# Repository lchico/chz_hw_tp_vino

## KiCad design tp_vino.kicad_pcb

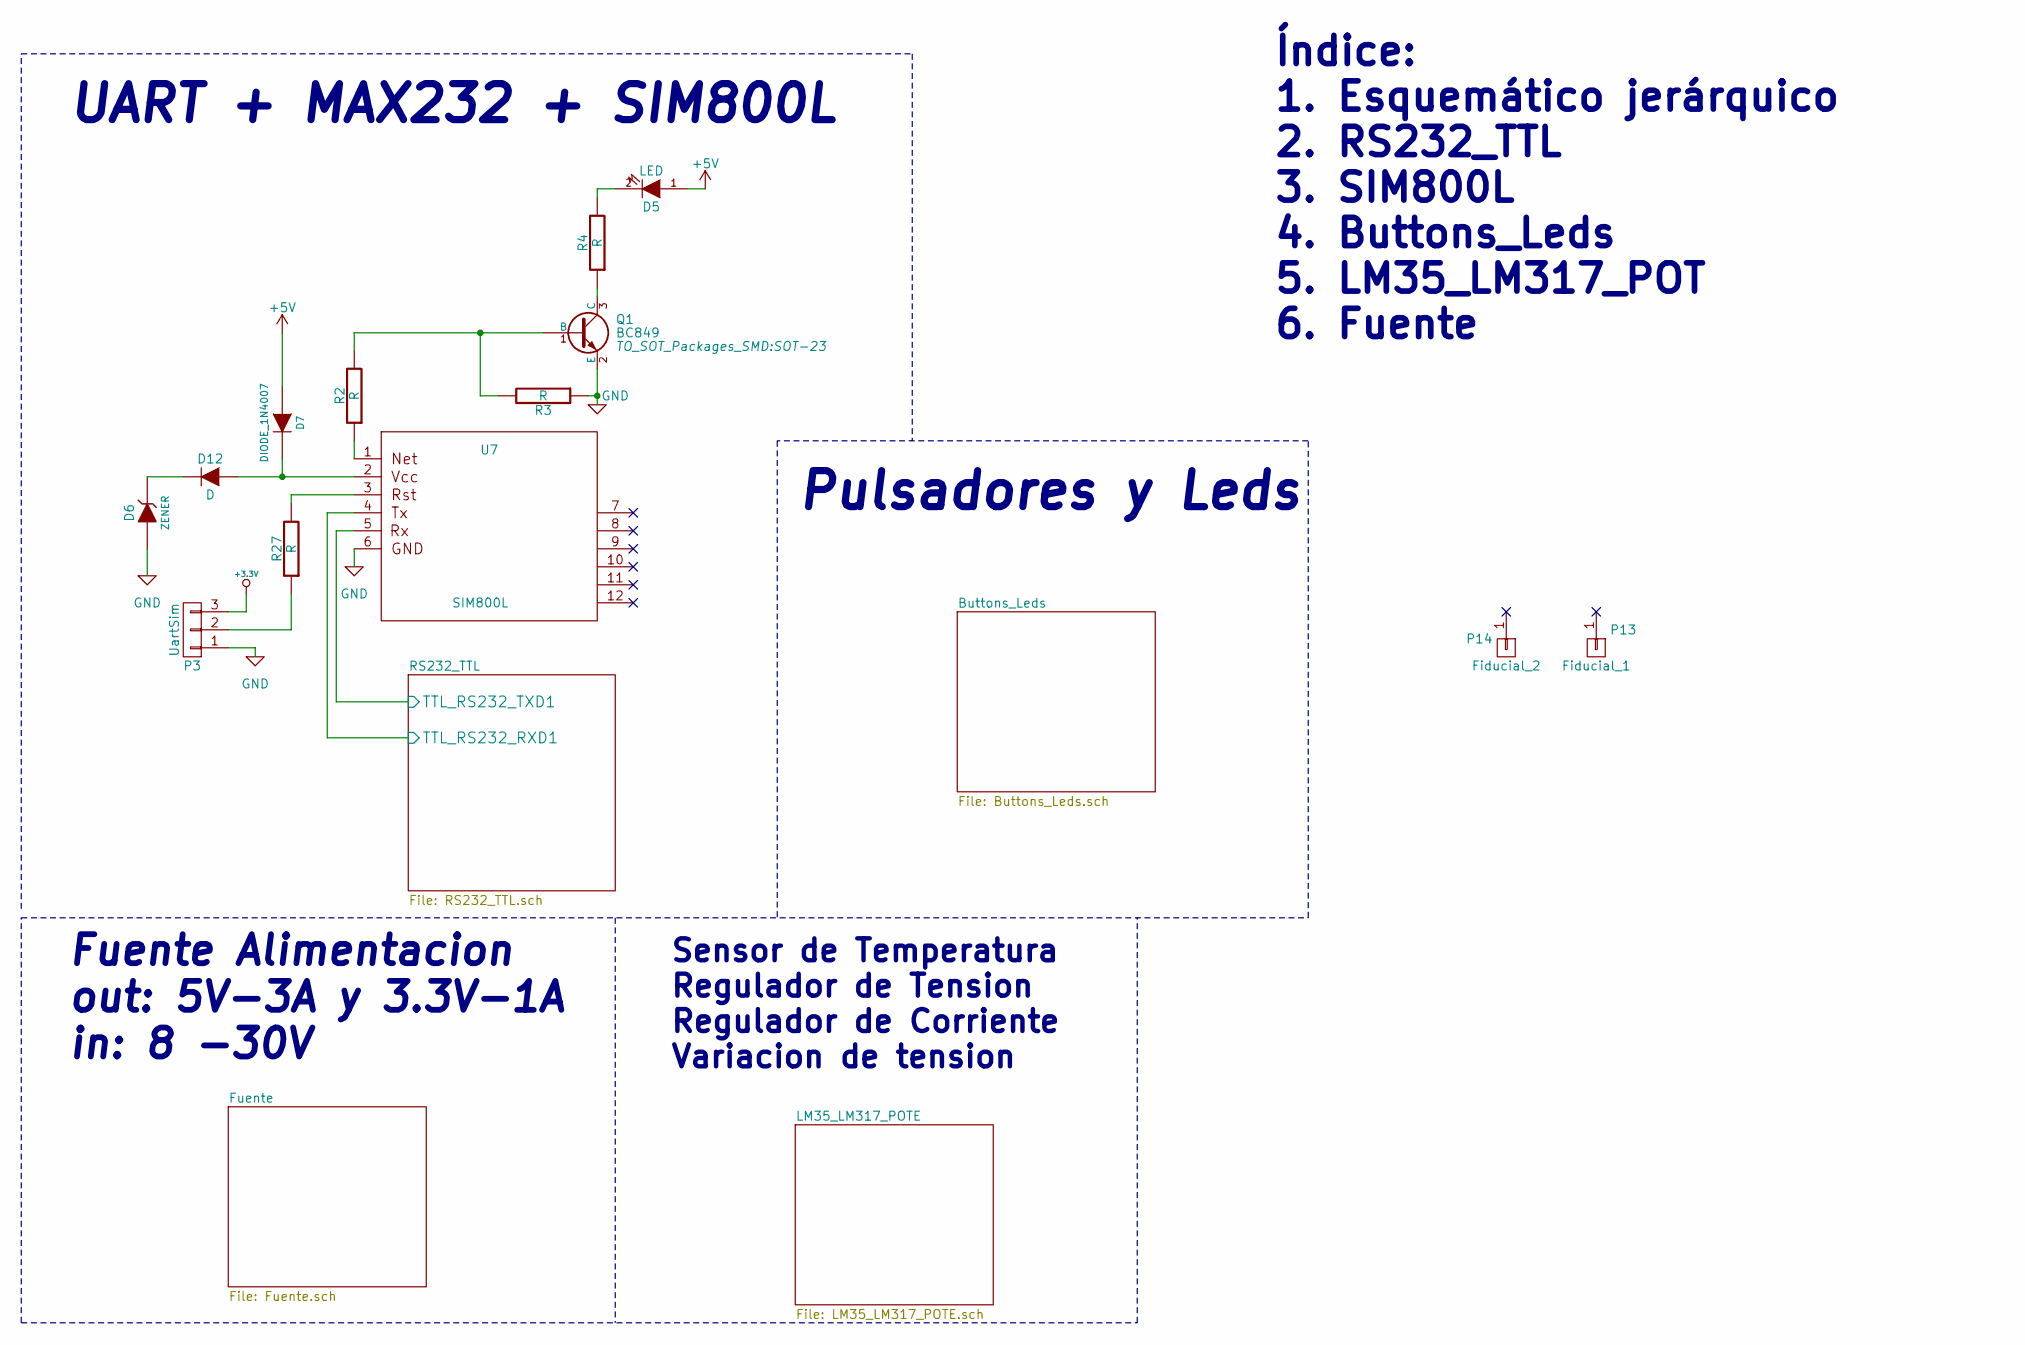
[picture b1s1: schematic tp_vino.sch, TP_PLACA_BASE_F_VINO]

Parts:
D5: LED; SMD-1206_Pol; Digikey SML-LX1206GC-TR SML-LX1206GC-TR
D6: ZENER; MELF_Standard
D7: DIODE_1N4007; MELF_Standard
D12: D; MELF_Standard
P3: UartSim; Pin_Header_Straight_1x03
P13: Fiducial_1
P14: Fiducial_2
Q1: BC849; SOT-23; Digikey# BC849BLT1GOSTR-ND
R2, R3, R4, R27: R; SMD-1206_Pol; Digikey# CRCW12060000Z0EA
U7: SIM800L; sim; Digikey# 1471-1458-ND

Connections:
+5V: D5.1 (A), D7.1 (A); also elsewhere on the board
/RS232_TTL/TTL_RS232_RXD1: U7.4; also elsewhere on the board
/RS232_TTL/TTL_RS232_TXD1: U7.5; also elsewhere on the board
GND: D6.1 (A), P3.1, Q1.2 (E), R3.1, U7.6; also elsewhere on the board
unnamed: D5.2 (K), R4.2
unnamed: D6.2 (K), D12.1 (K)
unnamed: D7.2 (K), D12.2 (A), U7.2
unnamed: P3.2, R27.1
unnamed: Q1.1 (B), R2.2, R3.2
unnamed: Q1.3 (C), R4.1
unnamed: R2.1, U7.1
unnamed: R27.2, U7.3

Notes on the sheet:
Índice: 1. Esquemático jerárquico 2. RS232_TTL 3. SIM800L 4. Buttons_Leds 5. LM35_LM317_POT 6. Fuente
Pulsadores y Leds
UART + MAX232 + SIM800L
Fuente Alimentacion out: 5V-3A y 3.3V-1A in: 8 -30V
Sensor de Temperatura Regulador de Tension Regulador de Corriente Variacion de tension

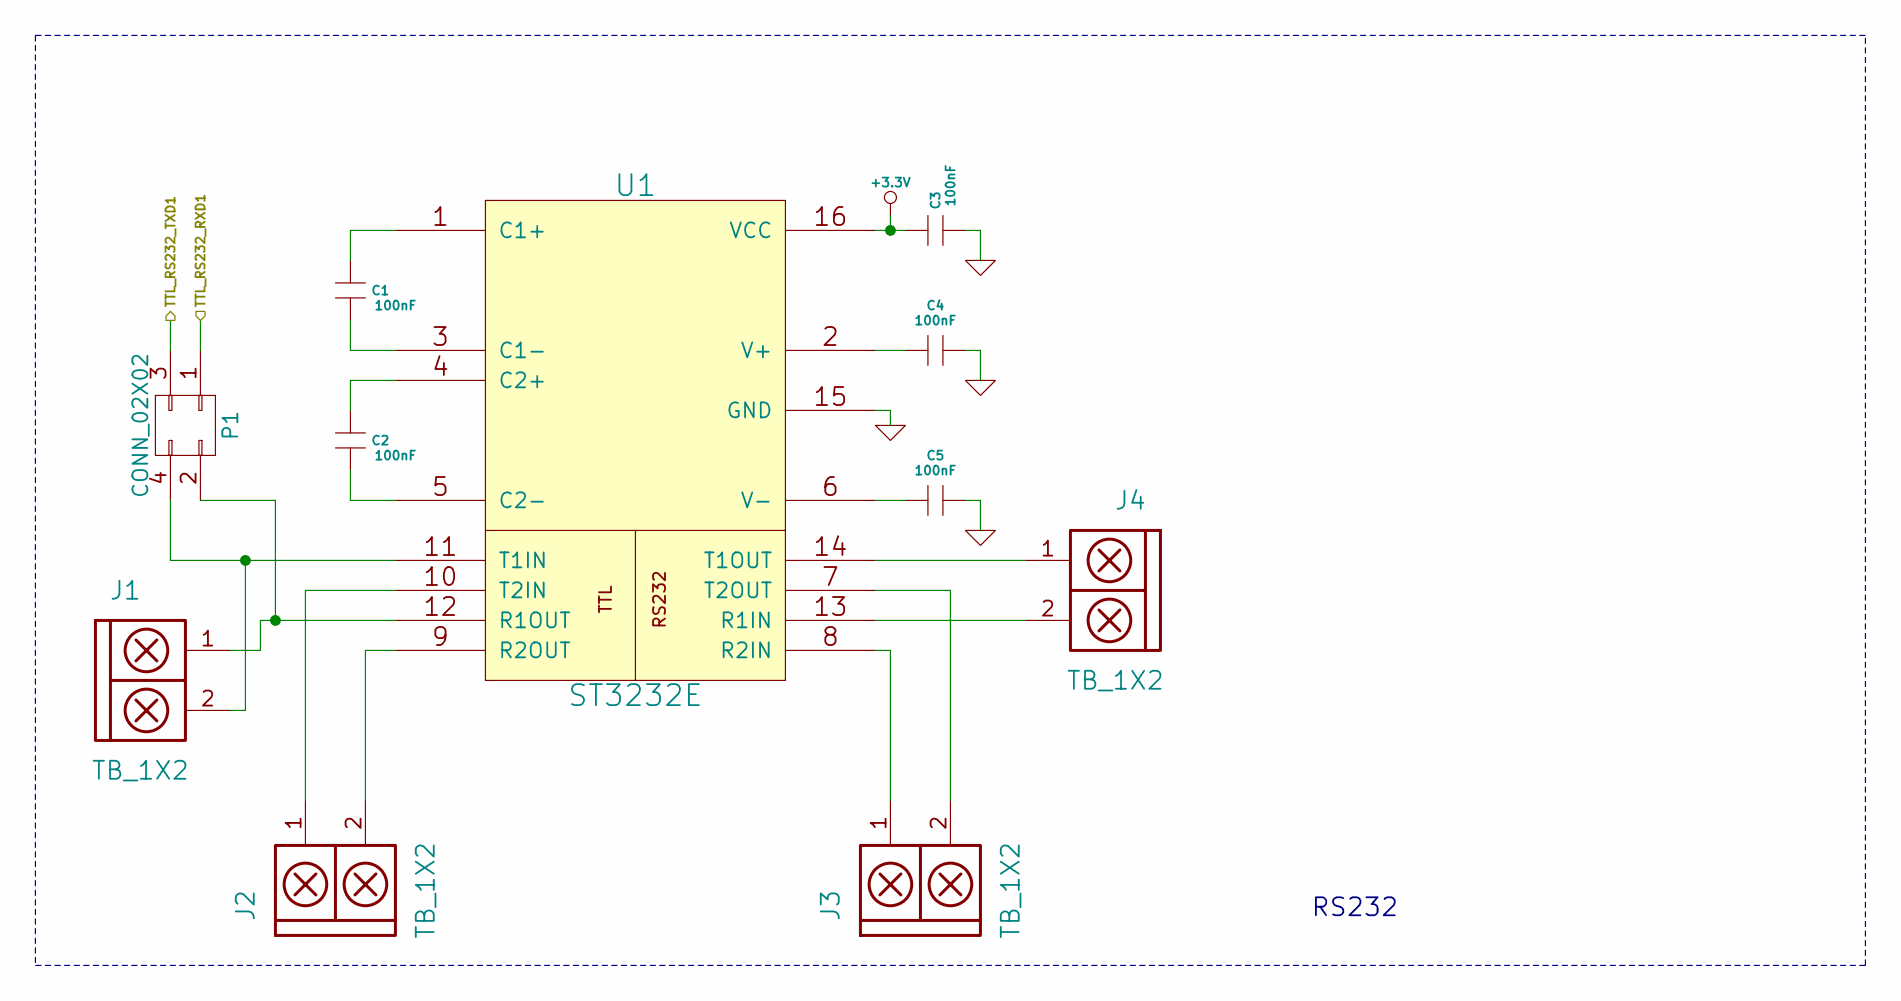
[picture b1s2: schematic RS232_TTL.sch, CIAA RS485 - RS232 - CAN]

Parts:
C1, C2, C3, C4, C5: 100nF; C_1206
J1, J2, J3, J4: TB_1X2; AK300-2
P1: CONN_02X02; Pin_Header_Straight_2x02
U1: ST3232E; SO-16-N

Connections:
/RS232_TTL/TTL_RS232_RXD1: P1.1; also elsewhere on the board
/RS232_TTL/TTL_RS232_TXD1: P1.3; also elsewhere on the board
GND: C3.2 (B), C4.2 (B), C5.2 (B), U1.15 (GND); also elsewhere on the board
unnamed: C1.1 (A), U1.1 (C1+)
unnamed: C1.2 (B), U1.3 (C1-)
unnamed: C2.1 (A), U1.4 (C2+)
unnamed: C2.2 (B), U1.5 (C2-)
unnamed: C4.1 (A), U1.2 (V+)
unnamed: C5.1 (A), U1.6 (V-)
unnamed: J1.1, P1.2, U1.12 (R1OUT)
unnamed: J1.2, P1.4, U1.11 (T1IN)
unnamed: J2.1, U1.10 (T2IN)
unnamed: J2.2, U1.9 (R2OUT)
unnamed: J3.1, U1.8 (R2IN)
unnamed: J3.2, U1.7 (T2OUT)
unnamed: J4.1, U1.14 (T1OUT)
unnamed: J4.2, U1.13 (R1IN)

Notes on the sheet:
RS232

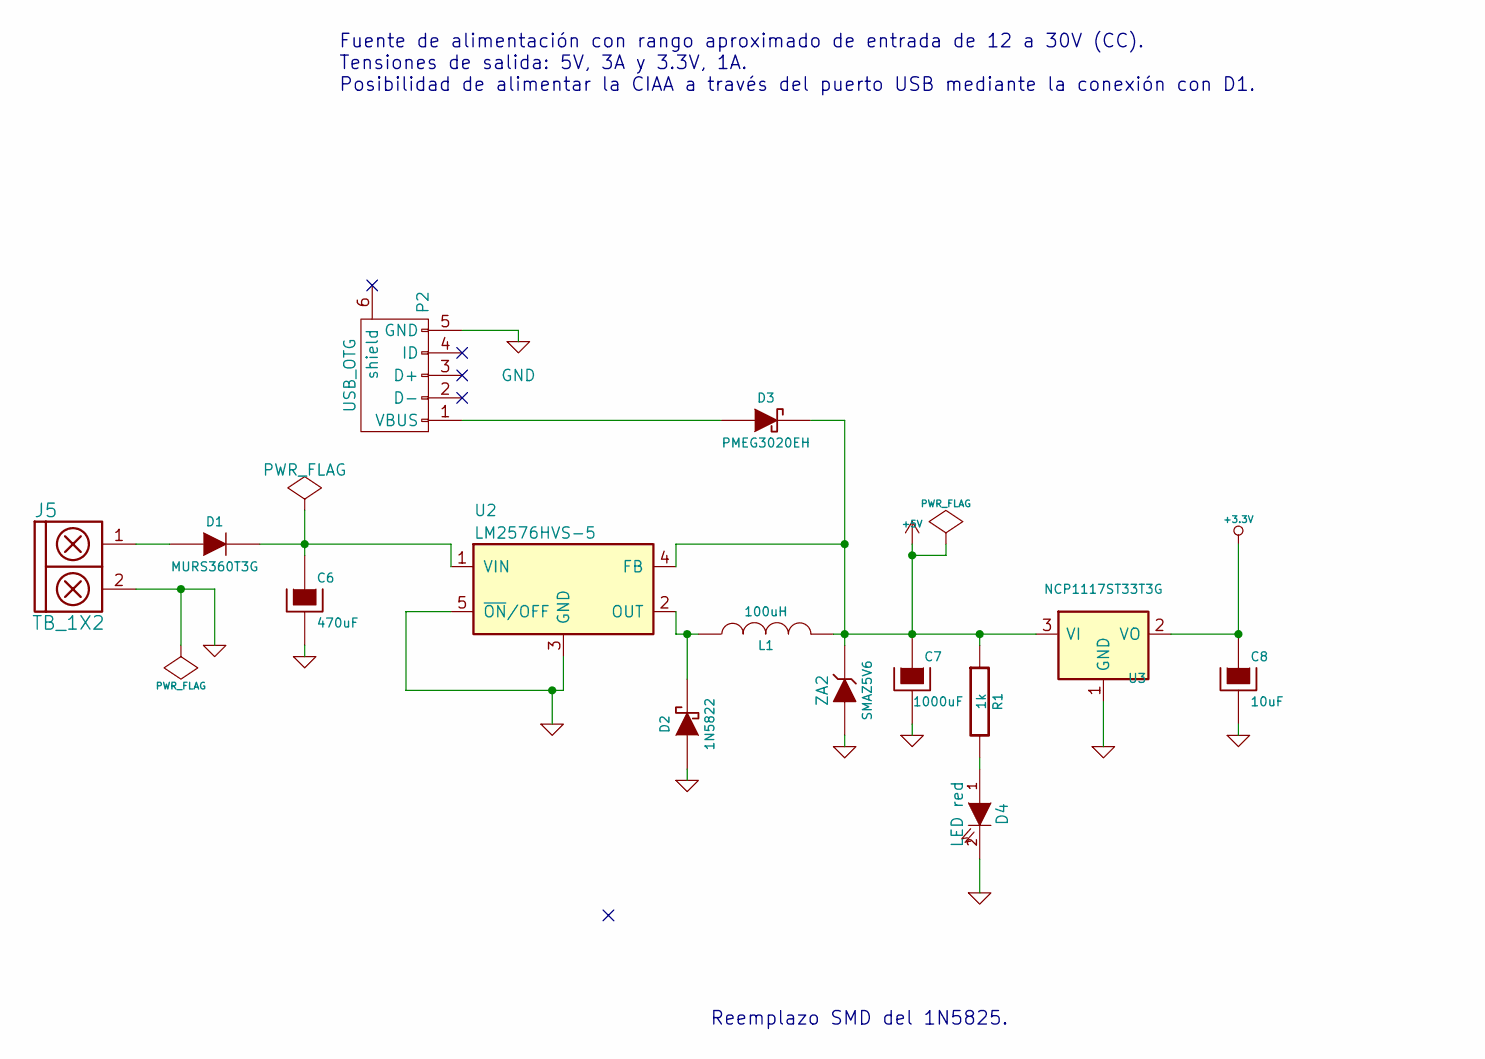
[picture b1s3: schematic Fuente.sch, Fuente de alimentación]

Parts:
C6: 470uF; C_Radial_D13_L21_P5
C7: 1000uF; C_Radial_D10_L20_P5
C8: 10uF; C_Radial_D10_L25_P5
D1: MURS360T3G; SOD-123
D2: 1N5822; SOD-123
D3: PMEG3020EH; SOD-123
D4: LED red; LED_1206
J5: TB_1X2; bornier2
L1: 100uH; INDUCTOR_V
P2: USB_OTG; USB_Micro-B
R1: 1k; SMD-1206_Pol
U2: LM2576HVS-5; TO-263-5Lead
U3: NCP1117ST33T3G; SOT-323
ZA2: SMAZ5V6; SMB_Handsoldering

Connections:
+5V: C7.1, D3.2 (K), L1.2, R1.1, U2.4 (FB), U3.3 (VI), ZA2.2 (K); also elsewhere on the board
GND: C6.2, C7.2, C8.2, D2.1 (A), D4.2 (K), J5.2, P2.5 (GND), U2.3 (GND), U2.5 (~ON~/OFF), U3.1 (GND), ZA2.1 (A); also elsewhere on the board
unnamed: C6.1, D1.2 (K), U2.1 (VIN)
unnamed: D1.1 (A), J5.1
unnamed: D2.2 (K), L1.1, U2.2 (OUT)
unnamed: D3.1 (A), P2.1 (VBUS)
unnamed: D4.1 (A), R1.2

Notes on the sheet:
Fuente de alimentación con rango aproximado de entrada de 12 a 30V (CC). Tensiones de salida: 5V, 3A y 3.3V, 1A. Posibilidad de alimentar la CIAA a través del puerto USB mediante la conexión con D1.
Reemplazo SMD del 1N5825.

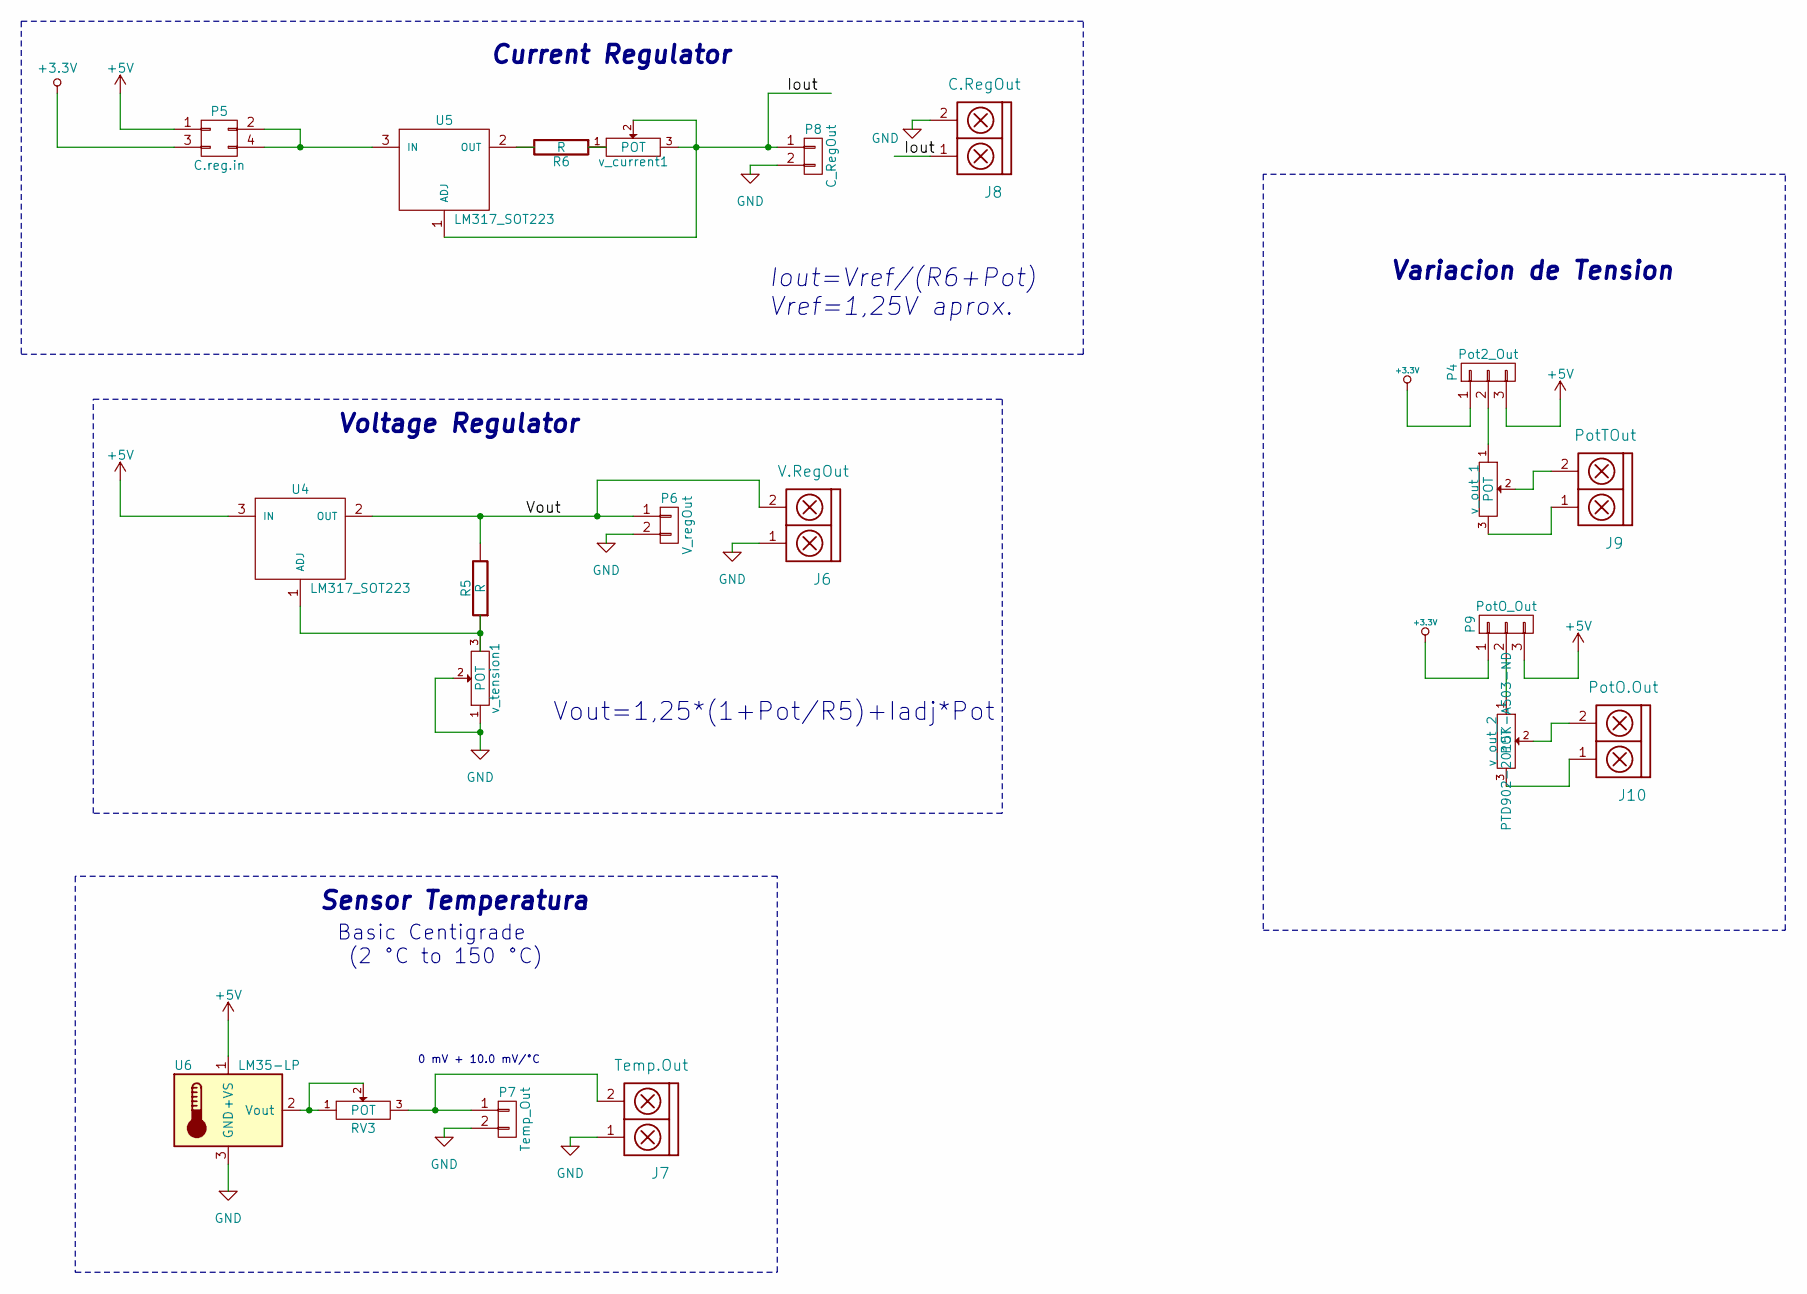
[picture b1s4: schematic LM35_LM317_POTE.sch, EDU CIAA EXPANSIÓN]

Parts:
J6: V.RegOut; AK300-2
J7: Temp.Out; AK300-2
J8: C.RegOut; AK300-2
J9: PotTOut; AK300-2
J10: PotO.Out; AK300-2
P4: Pot2_Out; Pin_Header_Straight_1x03
P5: C.reg.in; Pin_Header_Straight_2x02
P6: V_regOut; Pin_Header_Straight_1x02
P7: Temp_Out; Pin_Header_Straight_1x02
P8: C_RegOut; Pin_Header_Straight_1x02
P9: PotO_Out; Pin_Header_Straight_1x03
R5, R6: R; SMD-1206_Pol
RV3: POT; Potentiometer_Alps-RK16-single; Digikey# A105870-ND
U4, U5: LM317_SOT223; TO-220_Neutral123_Vertical; Digikey# LM317TFS-ND
U6: LM35-LP; TO-92_Inline_Wide; Digikey# LM35DZ/NOPB-ND
v_current1: POT; Potentiometer_Bourns_3296W_3-8Zoll_Inline_ScrewUp; Digikey# PTD902-2015K-A503-ND
v_out_1, v_out_2: POT; Potentiometer_Alps-RK16-single_largePads; Digikey# PTD902-2015K-A503-ND
v_tension1: POT; Potentiometer_Bourns_3296W_3-8Zoll_Inline_ScrewUp; Digikey# PTD902-2015K-A503-ND

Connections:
+5V: P4.3, P5.1, P9.3, U4.3 (IN), U6.1 (+VS); also elsewhere on the board
/LM35_LM317_POTE/Iout: J8.1, P8.1, U5.1 (ADJ), v_current1.2, v_current1.3
/LM35_LM317_POTE/Vout: J6.2, P6.1, R5.2, U4.2 (OUT)
GND: J6.1, J7.1, J8.2, P6.2, P7.2, P8.2, U6.3 (GND), v_tension1.1, v_tension1.2; also elsewhere on the board
unnamed: J7.2, P7.1, RV3.3
unnamed: J9.1, v_out_1.3
unnamed: J9.2, v_out_1.2
unnamed: J10.1, v_out_2.3
unnamed: J10.2, v_out_2.2
unnamed: P4.2, v_out_1.1
unnamed: P5.2, P5.4, U5.3 (IN)
unnamed: P9.2, v_out_2.1
unnamed: R5.1, U4.1 (ADJ), v_tension1.3
unnamed: R6.1, v_current1.1
unnamed: R6.2, U5.2 (OUT)
unnamed: RV3.1, RV3.2, U6.2 (Vout)

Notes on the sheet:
Current Regulator
Iout=Vref/(R6+Pot) Vref=1,25V aprox.
Vout=1,25*(1+Pot/R5)+Iadj*Pot
Voltage Regulator
Sensor Temperatura
Variacion de Tension
Basic Centigrade (2 °C to 150 °C)
0 mV + 10.0 mV/°C

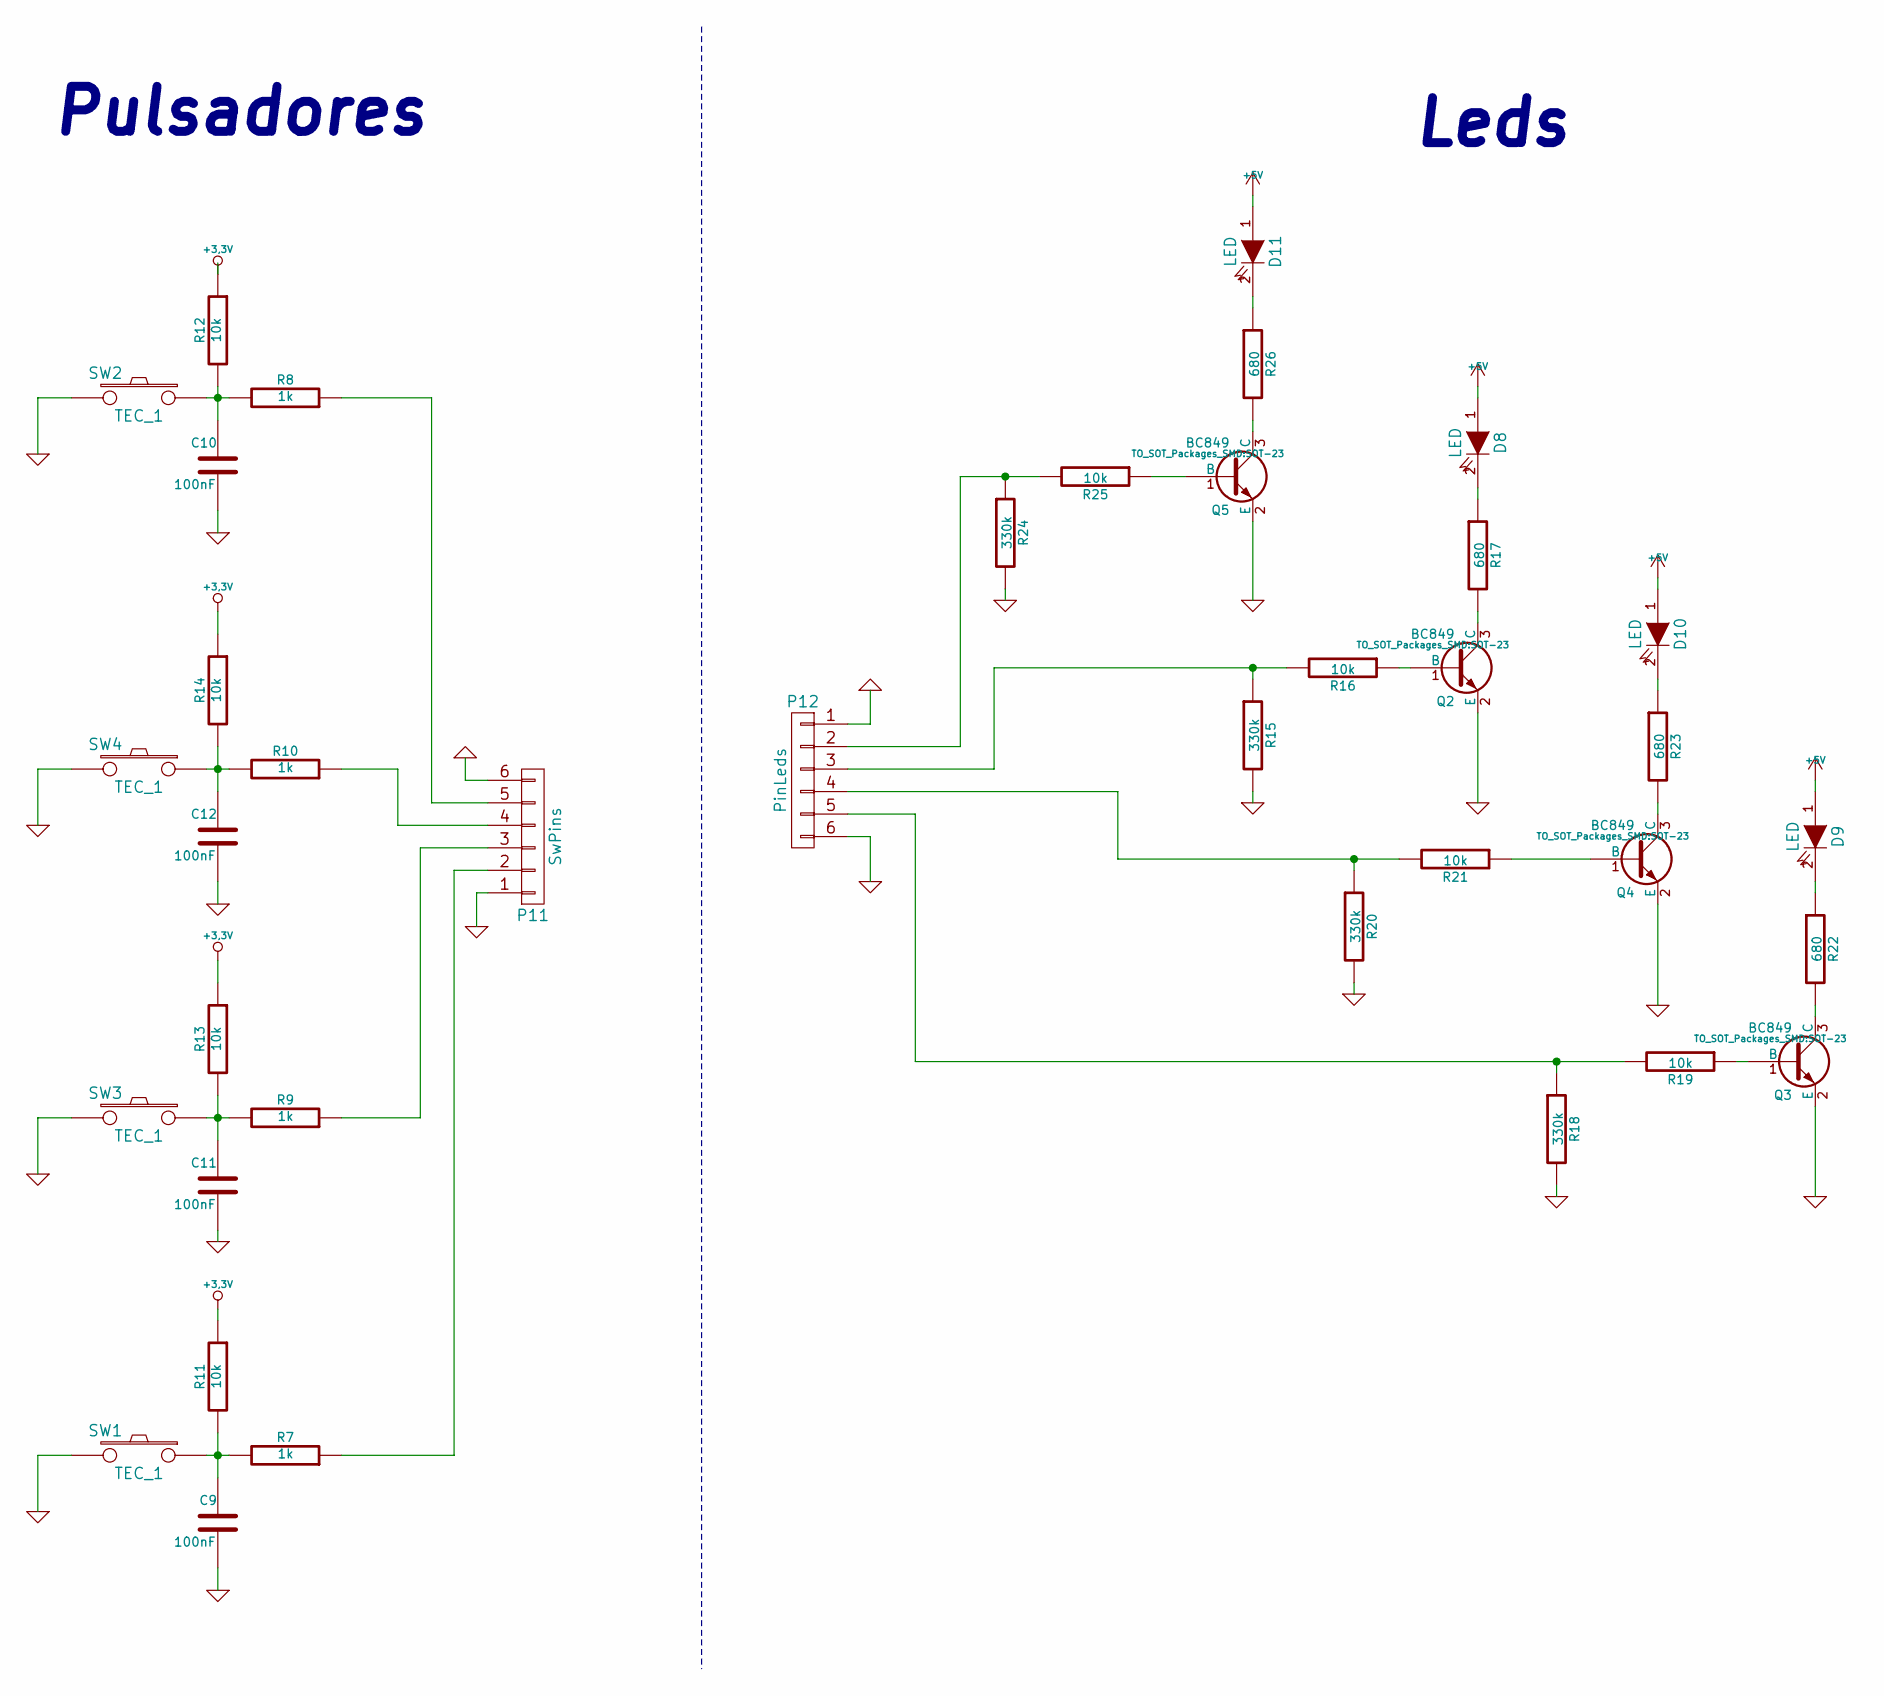
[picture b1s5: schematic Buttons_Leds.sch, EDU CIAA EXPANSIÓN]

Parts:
C9, C10, C11, C12: 100nF; C_1206; Digikey# 399-1167-1-ND
D8, D9, D10, D11: LED; SMD-1206_Pol; Digikey# 1080-1410-1-ND
P11: SwPins; Pin_Header_Straight_1x06; Digikey# 1528-1074-ND
P12: PinLeds; Pin_Header_Straight_1x06; Digikey# 1528-1074-ND
Q2, Q3, Q4, Q5: BC849; SOT-23; Digikey# BC849BLT1GOSTR-ND
R7, R8, R9, R10: 1k; SMD-1206_Pol; Digikey# 311-1.0KARCT-ND
R11, R12, R13, R14, R16, R19, R21, R25: 10k; SMD-1206_Pol; Digikey# P10KACT-ND
R15, R18, R20, R24: 330k; SMD-1206_Pol; Digikey# RMCF0805JT330KCT-ND
R17, R22, R23, R26: 680; SMD-1206_Pol; Digikey# RR12P680DCT-ND
SW1, SW2, SW3, SW4: TEC_1; SW_SPST_KMR2; Digikey# 450-1804-ND

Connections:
+5V: D8.1 (A), D9.1 (A), D10.1 (A), D11.1 (A); also elsewhere on the board
GND: C9.2, C10.2, C11.2, C12.2, P11.1, P11.6, P12.1, P12.6, Q2.2 (E), Q3.2 (E), Q4.2 (E), Q5.2 (E), R15.2, R18.2, R20.2, R24.2, SW1.2, SW2.2, SW3.2, SW4.2; also elsewhere on the board
unnamed: C9.1, R7.2, R11.2, SW1.1
unnamed: C10.1, R8.2, R12.2, SW2.1
unnamed: C11.1, R9.2, R13.2, SW3.1
unnamed: C12.1, R10.2, R14.2, SW4.1
unnamed: D8.2 (K), R17.1
unnamed: D9.2 (K), R22.1
unnamed: D10.2 (K), R23.1
unnamed: D11.2 (K), R26.1
unnamed: P11.2, R7.1
unnamed: P11.3, R9.1
unnamed: P11.4, R10.1
unnamed: P11.5, R8.1
unnamed: P12.2, R24.1, R25.2
unnamed: P12.3, R15.1, R16.2
unnamed: P12.4, R20.1, R21.2
unnamed: P12.5, R18.1, R19.2
unnamed: Q2.1 (B), R16.1
unnamed: Q2.3 (C), R17.2
unnamed: Q3.1 (B), R19.1
unnamed: Q3.3 (C), R22.2
unnamed: Q4.1 (B), R21.1
unnamed: Q4.3 (C), R23.2
unnamed: Q5.1 (B), R25.1
unnamed: Q5.3 (C), R26.2

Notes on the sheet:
Pulsadores
Leds

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
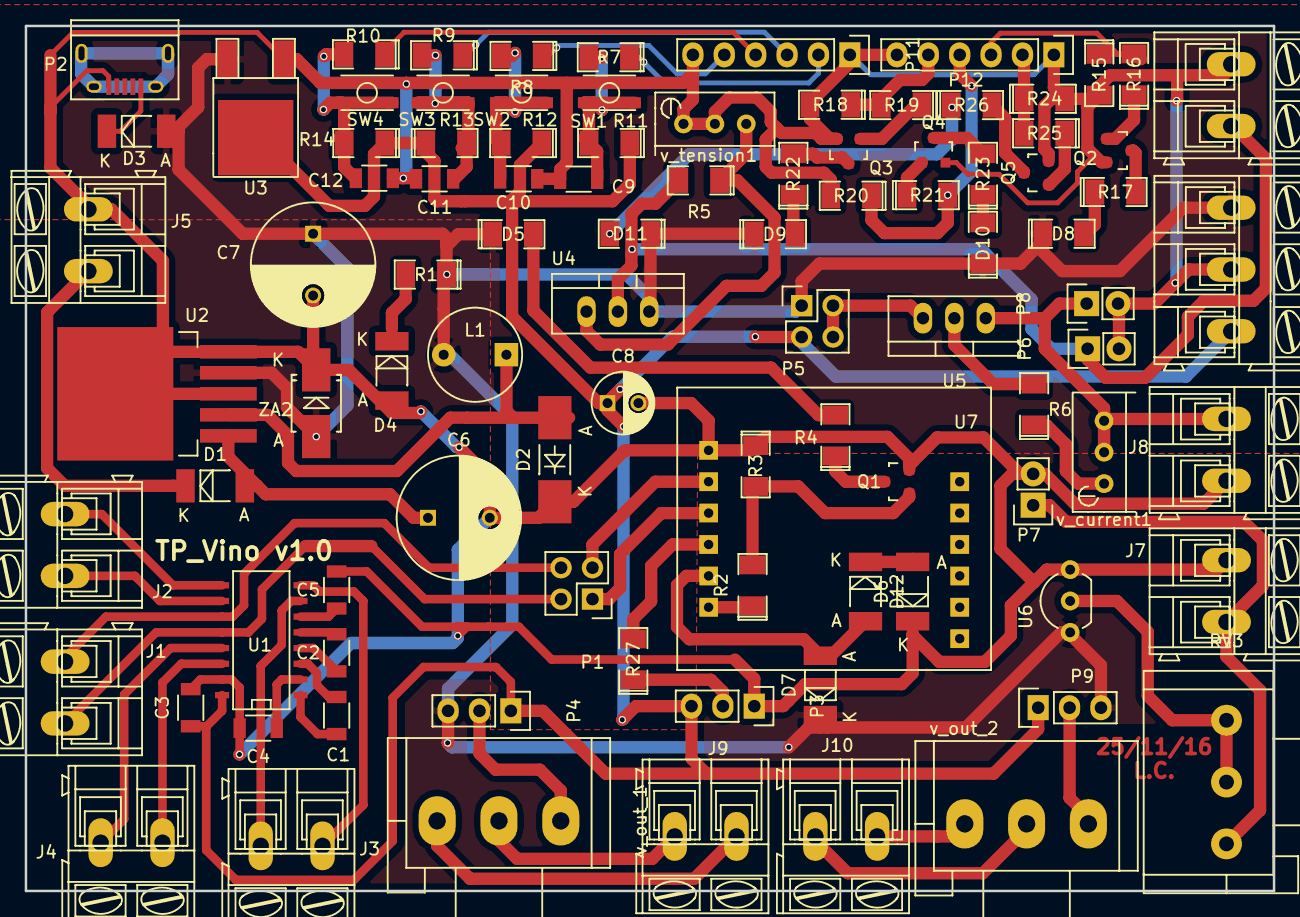
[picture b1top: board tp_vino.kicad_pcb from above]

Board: 2 copper layers, 101.0 x 70.0 mm, 96 parts (0 on the bottom side), 70 nets.

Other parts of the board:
P10: 3.3v_GNF_5v; AK300-3

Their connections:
+5V: P10.1; also elsewhere on the board
GND: P10.2; also elsewhere on the board

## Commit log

2016-11-02 Arreglo Max3232_ok, Fuente_ok, Buttons&Leds, OK. Fuente correinte OK, Potenciometros OK y LM35 OK.
2016-11-02 Adiciono datasheets. Y reordeno Carpetas.
2016-11-03 Modifico algunos componentes. Seteo algunos encapsulados. Ordeno los componentes en el PCB.
2016-11-04 Algunas modificaciones en el circuito oreno el pcb.
2016-11-04 Modificaciones en el schematic debida a los warning por powerflag y conectores mal definido como input en vez de pasive.
2016-11-08 Modificaciones en el schematic dado los componentes comprados empiezo a ordenar los componentes en una dimension estimada de 10x6 cm.
2016-11-08 Modificaciones en el schematico.Cambio dimension a 10x7 cm.
2016-11-08 Ruteo del PCB, agrego una salida de 5v y 3v en el esquematico
2016-11-08 Ruteo del PCB top first end. Falta button layer
2016-11-09 Ruteo del PCB top and button end. First Version
2016-11-09 Change names schematic.
2016-11-09 Agrego los graficos para el esquematico en 3d.
2016-12-15 Add digikey code and comment schematic.
2016-12-24 Actualizo las revisiones y documentaciones faltante. Algunas correcciones realizadas, faltan algunas mas que vere de hacerlas.
